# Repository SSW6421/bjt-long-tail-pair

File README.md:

# ⚡ BJT Long-Tail Pair (Differential Amplifier) — Hardware & Simulation Design

**Author:** Sithum Sathsara Vitharana &nbsp;|&nbsp; **Reg. No:** E/21/420  
**Course:** EE403 / EE559 — Integrated Analog Electronic Circuits &nbsp;|&nbsp; **Department:** Electrical & Electronic Engineering, University of Peradeniya

---

## 📌 Project Overview

This repository contains the design, simulation, and hardware PCB implementation of a **BJT Long-Tail Pair (Differential Amplifier)** using matched dual transistors (**SSM2212 SMD**).

The project covers theoretical design, circuit simulation across operating regimes in **Qucs**, and schematic capture / PCB layout in **KiCad**.

---

## 🎯 Objectives & Key Observations

1. **Circuit Design & Sizing:** Design a balanced differential pair and current mirror tail for target operating point and power rails ($\pm 5\text{ V}$).
2. **Simulation Analysis (Qucs):**
   - DC transfer characteristics and differential voltage gain ($A_d$)
   - Common-mode response and Common Mode Rejection Ratio (CMRR)
   - Frequency response and $-3\text{ dB}$ bandwidth
   - Maximum undistorted output voltage swing
3. **Hardware Implementation (KiCad PCB):**
   - Professional schematic capture using surface-mount components (SMD 1206 resistors & SOIC-8 dual BJTs)
   - Custom PCB layout for low parasitic interference and symmetry

---

## 🛠️ Components & Tools

| Category | Details |
|----------|---------|
| **Active Components** | SSM2212 matched NPN dual transistor pairs (SOIC-8 SMD) |
| **Passive Components** | SMD 1206 precision resistors ($680\ \Omega$, $1.8\ \text{k}\Omega$, $6.8\ \text{k}\Omega$, $10\ \text{k}\Omega$) |
| **Power Rails** | Dual supply ($\pm 5\text{ V}$) |
| **Circuit Simulation** | [Qucs](http://qucs.sourceforge.net/) (Quite Universal Circuit Simulator) |
| **PCB CAD Tool** | [KiCad](https://www.kicad.org/) (Schematic & 2-Layer PCB Layout) |

---

## 📁 Repository Structure

```
bjt-long-tail-pair/
│
├── kicad/
│   └── long_tail_pair/
│       ├── long_tail_pair.kicad_pro   # KiCad project file
│       ├── long_tail_pair.kicad_sch   # Differential amplifier schematic
│       └── long_tail_pair.kicad_pcb   # 2-layer PCB layout
│
├── simulation/
│   └── qucs/
│       ├── Mini_Project.sch           # Differential gain & DC sweep simulation
│       ├── Mini_Project_B.sch         # AC bandwidth & frequency response
│       ├── Mini_Project_C.sch         # Common-mode voltage & CMRR analysis
│       ├── Mini_Project_D.sch         # Extended parameter variations
│       ├── *.dpl                      # Simulation plot configurations
│       └── netlist.txt                # Exported SPICE/Qucs netlist
│
├── docs/
│   ├── project_report.pdf             # Comprehensive project report (EE403)
│   └── schematic.pdf                  # Exported vector schematic diagram
│
├── .gitignore
└── README.md
```

---

## 🔬 Circuit Architecture

The amplifier consists of:
- **Differential Pair:** Matched NPN pair with emitter degeneration / common-emitter connection.
- **Tail Current Source:** Current mirror configuration using matched SSM2212 transistors to provide high dynamic output impedance, maximizing CMRR.
- **Load:** Matched collector resistors ($R_{C1}, R_{C2}$) delivering balanced differential output ($V_{od} = V_{out1} - V_{out2}$).

---

## 🚀 How to Open & Inspect

### KiCad Project:
1. Install [KiCad 7 or 8](https://www.kicad.org/download/).
2. Open `kicad/long_tail_pair/long_tail_pair.kicad_pro`.
3. Open the schematic (`.kicad_sch`) or PCB editor (`.kicad_pcb`).

### Qucs Simulation:
1. Install [Qucs](http://qucs.sourceforge.net/).
2. Open any schematic file in `simulation/qucs/` (e.g. `Mini_Project.sch`).
3. Press **F2** to simulate and view the data displays.

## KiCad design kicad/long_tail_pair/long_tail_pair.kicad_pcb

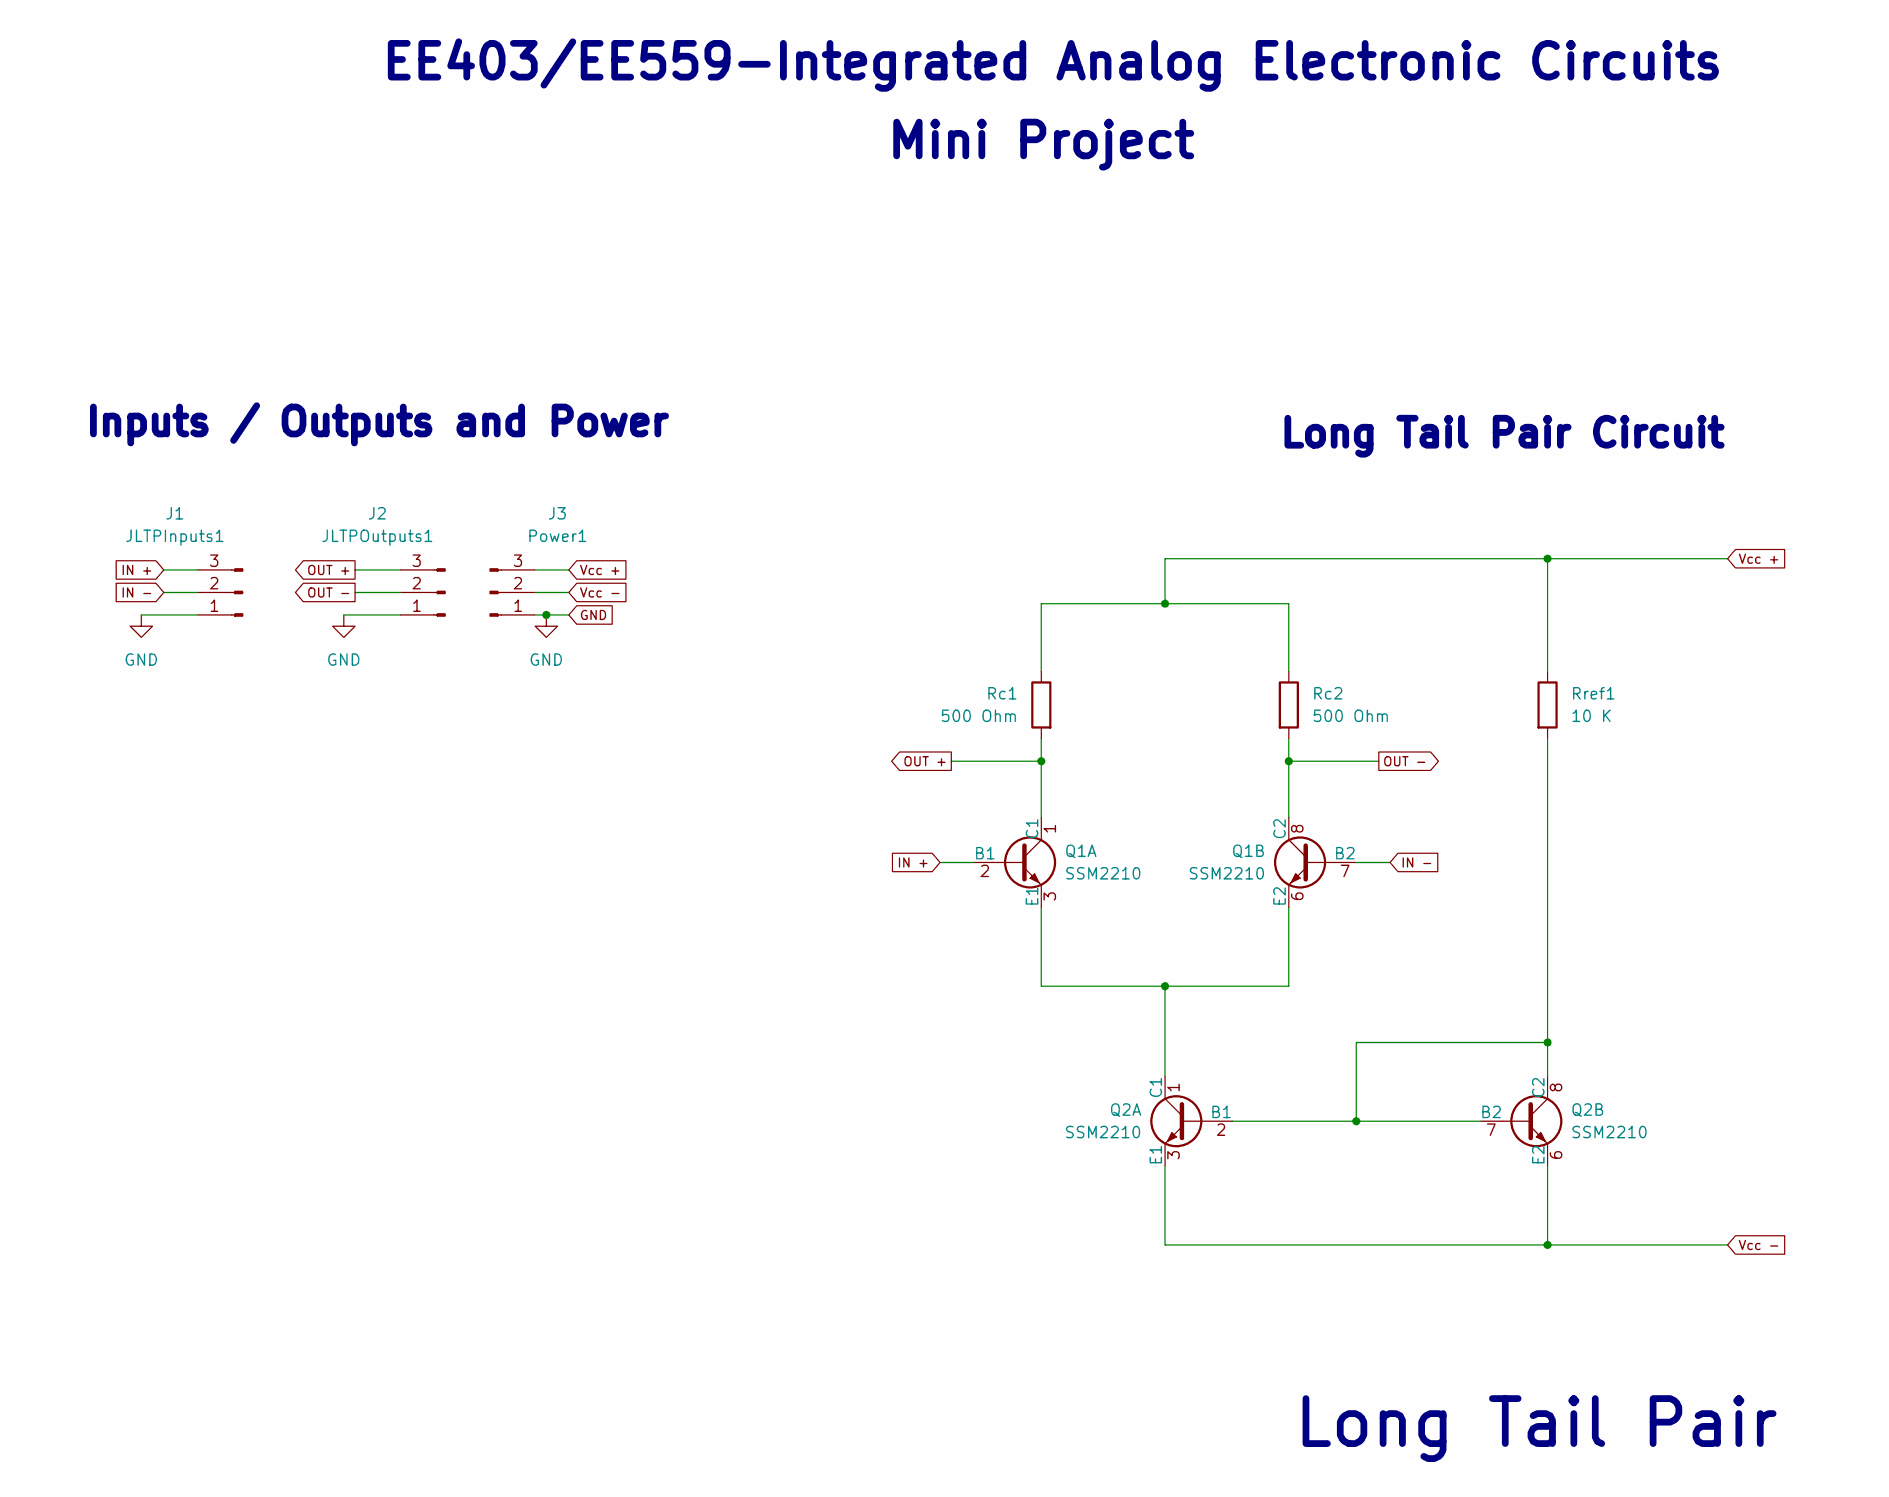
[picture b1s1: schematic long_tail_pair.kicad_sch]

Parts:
JLTPInputs1: J1; SolderWire-1.5sqmm_1x03_P7.8mm_D1.7mm_OD3.9mm
JLTPOutputs1: J2; SolderWire-1.5sqmm_1x03_P7.8mm_D1.7mm_OD3.9mm
Power1: J3; SolderWire-1.5sqmm_1x03_P7.8mm_D1.7mm_OD3.9mm
Q1, Q2: SSM2210; SOIC-8_3.9x4.9mm_P1.27mm
Rc1, Rc2: 500 Ohm; R_Axial_DIN0309_L9.0mm_D3.2mm_P12.70mm_Horizontal
Rref1: 10 K; R_Axial_DIN0309_L9.0mm_D3.2mm_P12.70mm_Horizontal

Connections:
GND: JLTPInputs1.1, JLTPOutputs1.1, Power1.1
IN +: JLTPInputs1.3, Q1.2 (B1)
IN -: JLTPInputs1.2, Q1.7 (B2)
unnamed: Q1.3 (E1), Q1.6 (E2), Q2.1 (C1)
unnamed: Q2.2 (B1), Q2.7 (B2), Q2.8 (C2), Rref1.2
OUT +: JLTPOutputs1.3, Q1.1 (C1), Rc1.2
OUT -: JLTPOutputs1.2, Q1.8 (C2), Rc2.2
Vcc +: Power1.3, Rc1.1, Rc2.1, Rref1.1
Vcc -: Power1.2, Q2.3 (E1), Q2.6 (E2)

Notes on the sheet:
Long Tail Pair
EE403/EE559-Integrated Analog Electronic Circuits
Mini Project
Inputs / Outputs and Power
Long Tail Pair Circuit

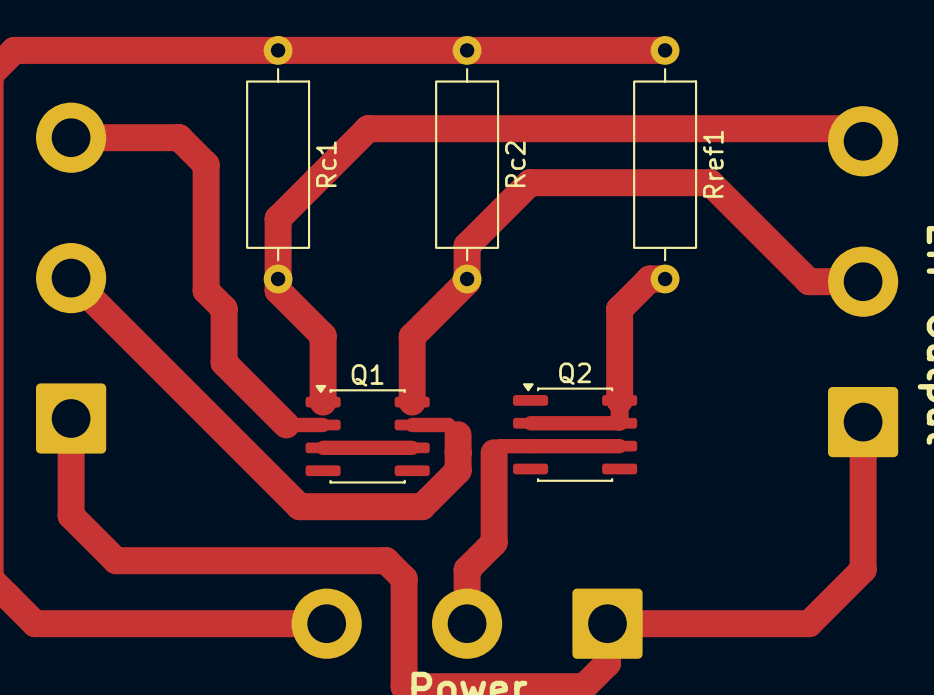
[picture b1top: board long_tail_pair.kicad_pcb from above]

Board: 2 copper layers, 8 parts (0 on the bottom side), 9 nets.
